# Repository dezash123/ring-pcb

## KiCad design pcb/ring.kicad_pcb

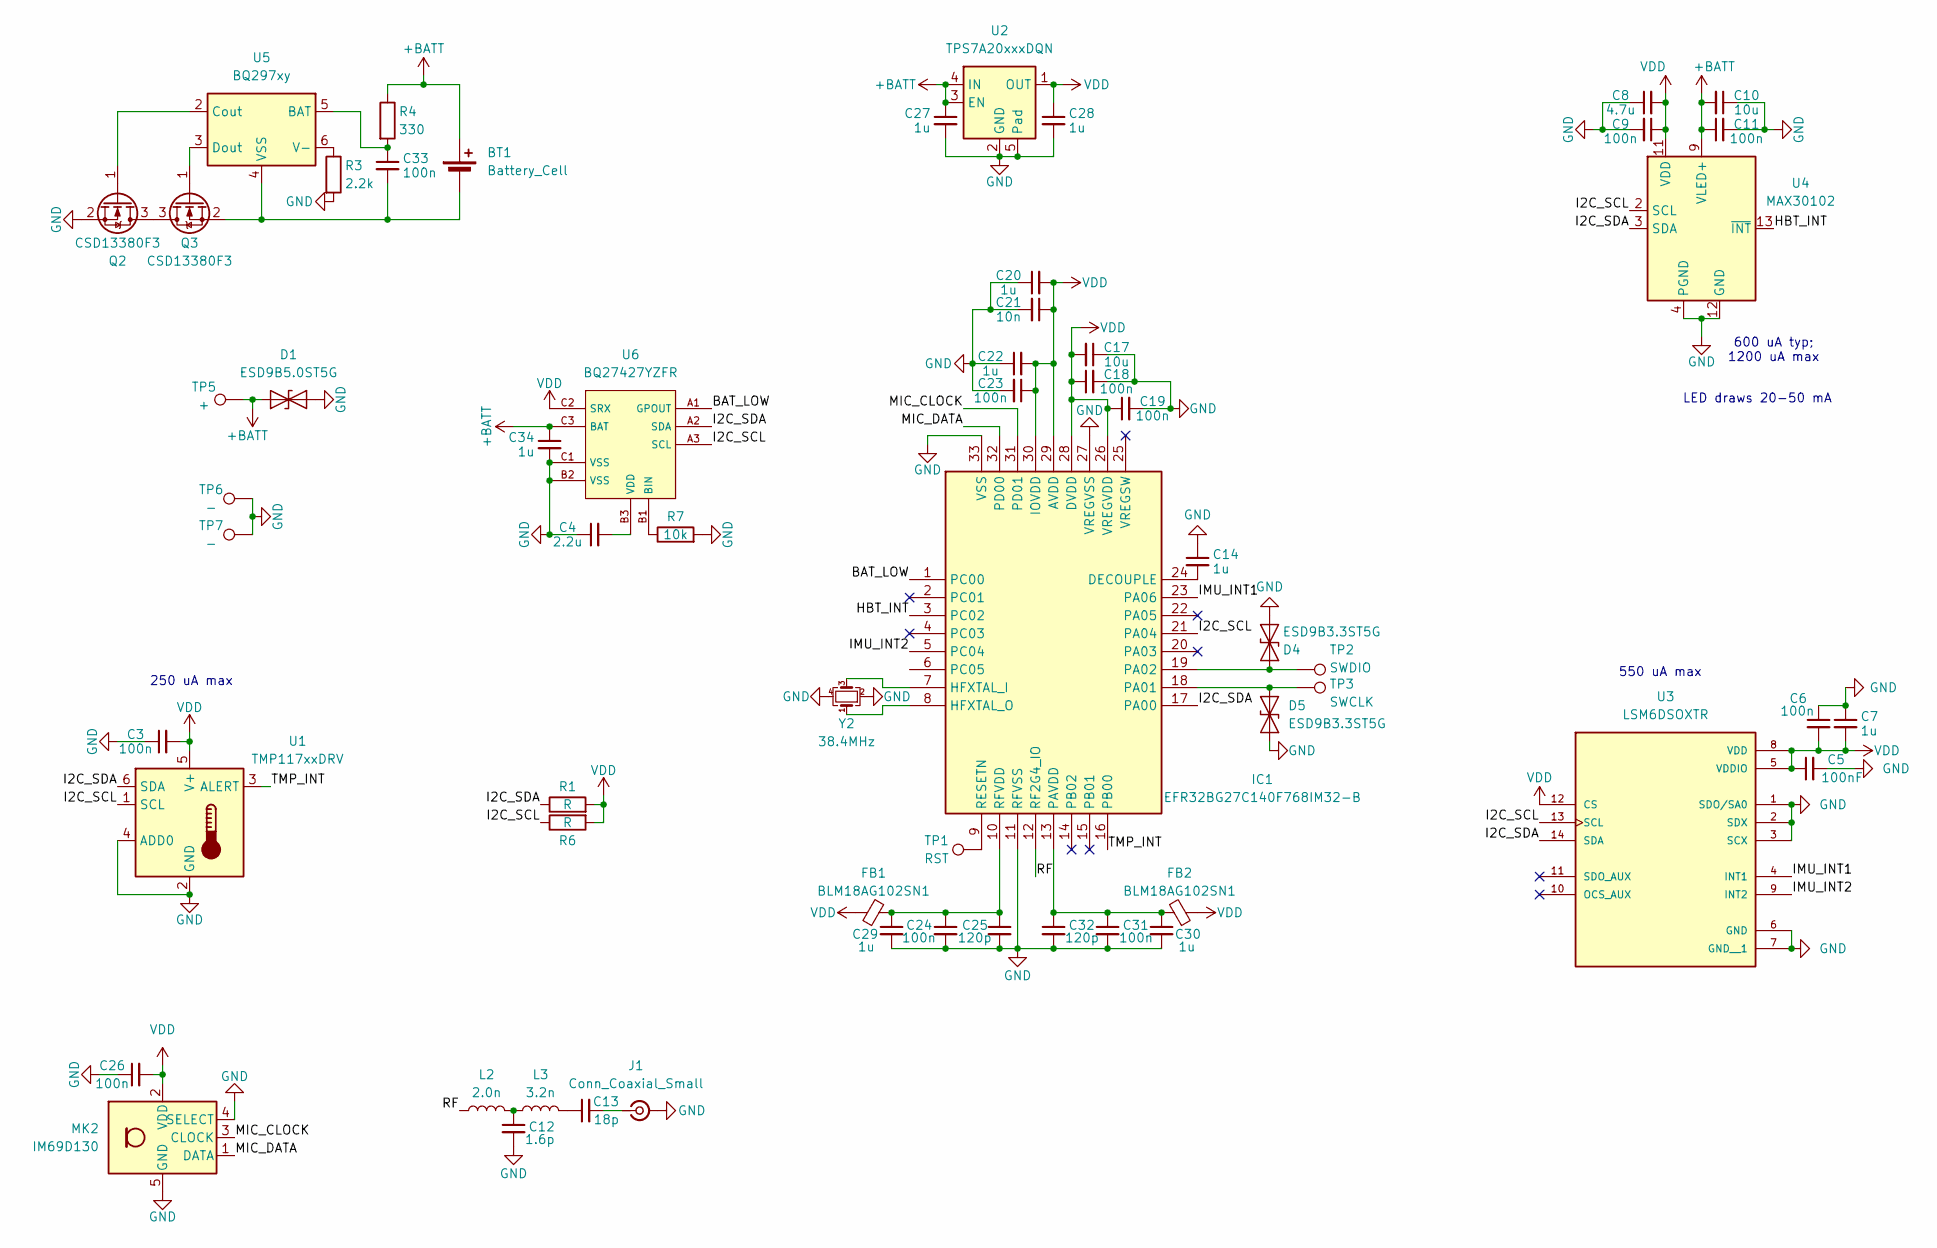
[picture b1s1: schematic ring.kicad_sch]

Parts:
BT1: Battery_Cell; Battery
C3: 100n; R_0201_0603Metric
C4: 2.2u; R_0201_0603Metric
C5: 100nF; C_0201_0603Metric
C6, C9, C11, C18, C19, C23, C24, C26, C31, C33: 100n; C_0201_0603Metric
C7, C14, C20, C22, C27, C28, C29, C30: 1u; C_0402_1005Metric
C8: 4.7u; C_0402_1005Metric
C10, C17: 10u; C_0402_1005Metric
C12: 1.6p; C_0201_0603Metric
C13: 18p; C_0201_0603Metric
C21: 10n; C_0201_0603Metric
C25, C32: 120p; C_0201_0603Metric
C34: 1u; C_0201_0603Metric
D1: ESD9B5.0ST5G; D_SOD-923
D4, D5: ESD9B3.3ST5G; D_SOD-923
FB1, FB2: BLM18AG102SN1; L_0603_1608Metric
IC1: EFR32BG27C140F768IM32-B; QFN-32-1EP_4x4mm_P0.4mm_EP2.9x2.9mm; Mouser Part Number 634-BG27C23068IM32-B
J1: Conn_Coaxial_Small; Texas_SWRA117D_2.4GHz_Right
L2: 2.0n; L_0201_0603Metric
L3: 3.2n; L_0201_0603Metric
MK2: IM69D130; Infineon_PG-LLGA-5-1
Q2, Q3: CSD13380F3; Texas_PicoStar_DFN-3_0.69x0.60mm
R1, R6: R; R_0201_0603Metric
R3: 2.2k; C_0201_0603Metric
R4: 330; C_0201_0603Metric
R7: 10k; R_0201_0603Metric
TP1: RST
TP2: SWDIO; TestPoint_Pad_D1.0mm
TP3: SWCLK; TestPoint_Pad_D1.0mm
TP5: +; TestPoint_Pad_D1.5mm
TP6, TP7: -; TestPoint_Pad_D1.0mm
U1: TMP117xxDRV; WSON-6-1EP_2x2mm_P0.65mm_EP1x1.6mm
U2: TPS7A20xxxDQN; Texas_X2SON-4_1x1mm_P0.65mm
U3: LSM6DSOXTR; LGA-14_3x2.5mm_P0.5mm_LayoutBorder3x4y; PARTREV 3.0
U4: MAX30102; Maxim_OLGA-14_3.3x5.6mm_P0.8mm
U5: BQ297xy; WSON-6_1.5x1.5mm_P0.5mm
U6: BQ27427YZFR; BGA-9_1.6x1.6mm_Layout3x3_P0.5mm
Y2: 38.4MHz; Crystal_SMD_1210-4Pin_1.2x1.0mm

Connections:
+BATT: BT1.1 (+), C10.2, C11.1, C27.1, C34.1, D1.1 (A1), R4.1, TP5.1, U2.3 (EN), U2.4 (IN), U4.9 (VLED+), U4.10 (VLED+), U6.C3 (BAT)
/BAT_LOW: IC1.1 (PC00), U6.A1 (GPOUT)
/HBT_INT: IC1.3 (PC02), U4.13 (~INT)
/I2C_SCL: IC1.21 (PA04), R6.1, U1.1 (SCL), U3.13 (SCL), U4.2 (SCL), U6.A3 (SCL)
/I2C_SDA: IC1.17 (PA00), R1.1, U1.6 (SDA), U3.14 (SDA), U4.3 (SDA), U6.A2 (SDA)
/IMU_INT1: IC1.23 (PA06), U3.4 (INT1)
/IMU_INT2: IC1.5 (PC04), U3.9 (INT2)
/MIC_CLOCK: IC1.31 (PD01), MK2.3 (CLOCK)
/MIC_DATA: IC1.32 (PD00), MK2.1 (DATA)
/RF: IC1.12 (RF2G4_IO), L2.1
/TMP_INT: IC1.16 (PB00), U1.3 (ALERT)
GND: C3.1, C4.1, C5.2, C6.1, C7.1, C8.1, C9.2, C10.1, C11.2, C12.2, C14.1, C17.1, C18.2, C19.2, C20.1, C21.2, C22.1, C23.2, C24.2, C25.2, C26.1, C27.2, C28.2, C29.2, C30.2, C31.2, C32.2, C34.2, D1.2 (A2), D4.2 (A2), D5.1 (A1), IC1.11 (RFVSS), IC1.27 (VREGVSS), IC1.33 (VSS), J1.2 (Ext), MK2.4 (SELECT), MK2.5 (GND), Q2.2 (S), R3.2, R7.2, TP6.1, TP7.1, U1.2 (GND), U1.4 (ADD0), U2.2 (GND), U2.5 (Pad), U3.1 (SDO/SA0), U3.2 (SDX), U3.3 (SCX), U3.6 (GND), U3.7 (GND__1), U4.4 (PGND), U4.12 (GND), U6.B2 (VSS), U6.C1 (VSS), Y2.2, Y2.4
unnamed: BT1.2 (-), C33.2, Q3.2 (S), U5.4 (VSS)
unnamed: C12.1, L2.2, L3.1
unnamed: C13.1, L3.2
unnamed: D4.1 (A1), IC1.19 (PA02), TP2.1
unnamed: D5.2 (A2), IC1.18 (PA01), TP3.1
unnamed: C14.2, IC1.24 (DECOUPLE)
unnamed: IC1.7 (HFXTAL_I), Y2.3
unnamed: IC1.8 (HFXTAL_O), Y2.1
unnamed: C30.1, C31.1, C32.1, FB2.2, IC1.13 (PAVDD)
unnamed: IC1.9 (RESETN), TP1.1
unnamed: C24.1, C25.1, C29.1, FB1.2, IC1.10 (RFVDD)
unnamed: C13.2, J1.1 (In)
unnamed: Q2.3 (D), Q3.3 (D)
unnamed: Q2.1 (G), U5.2 (Cout)
unnamed: Q3.1 (G), U5.3 (Dout)
unnamed: C33.1, R4.2, U5.5 (BAT)
unnamed: R3.1, U5.6 (V-)
unnamed: R7.1, U6.B1 (BIN)
unnamed: C4.2, U6.B3 (VDD)
VDD: C3.2, C5.1, C6.2, C7.2, C8.2, C9.1, C17.2, C18.1, C19.1, C20.2, C21.1, C22.2, C23.1, C26.2, C28.1, FB1.1, FB2.1, IC1.26 (VREGVDD), IC1.28 (DVDD), IC1.29 (AVDD), IC1.30 (IOVDD), MK2.2 (VDD), R1.2, R6.2, U1.5 (V+), U2.1 (OUT), U3.5 (VDDIO), U3.8 (VDD), U3.12 (CS), U4.11 (VDD), U6.C2 (SRX)

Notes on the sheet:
LED draws 20-50 mA
250 uA max
550 uA max
600 uA typ; 1200 uA max

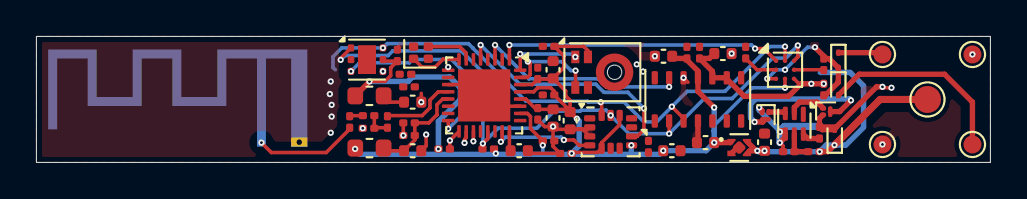
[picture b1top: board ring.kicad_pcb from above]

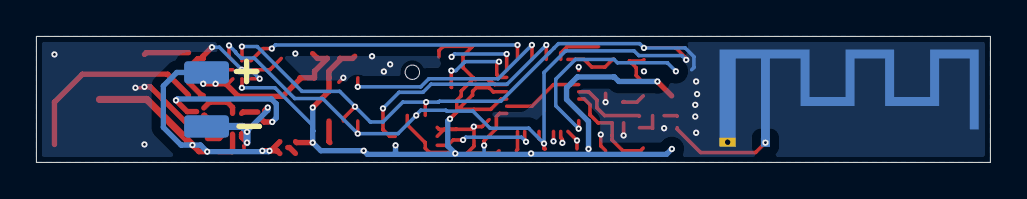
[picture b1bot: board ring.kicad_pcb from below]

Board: 2 copper layers, 53.0 x 7.0 mm, 60 parts (2 on the bottom side), 31 nets.

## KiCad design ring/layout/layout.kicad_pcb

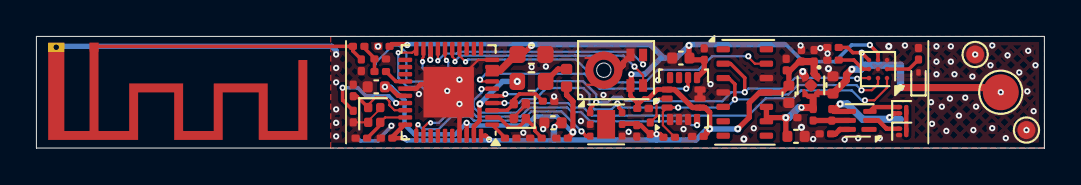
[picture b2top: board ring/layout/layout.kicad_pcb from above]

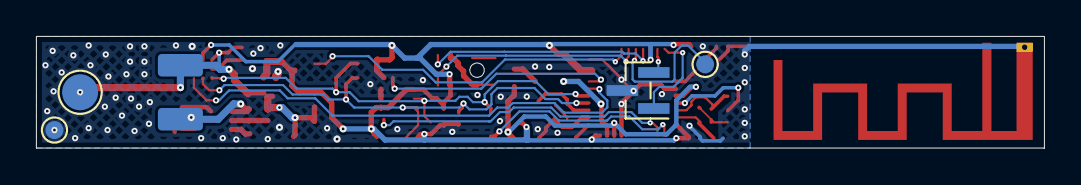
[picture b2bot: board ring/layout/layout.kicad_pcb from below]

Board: 2 copper layers, 56.0 x 6.2 mm, 60 parts (5 on the bottom side), 36 nets.

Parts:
BT1: ?; Battery
C1, C28, C29: 1uF; C_0201_0603Metric
C2: 2.2uF; C_0201_0603Metric
C3, C7, C8, C12, C19, C21, C22, C23, C25, C26: 100nF; C_0201_0603Metric
C4, C9: 5pF; C_0201_0603Metric
C5: 4.7uF; C_0603_1608Metric
C6, C14, C24, C27: 1uF; C_0402_1005Metric
C10, C11: 12pF; C_0201_0603Metric
C13: 100pF; C_0201_0603Metric
C15: 47nF; C_0201_0603Metric
C16: 1pF; C_0201_0603Metric
C17: 1.2pF; C_0201_0603Metric
C18: 10uF; C_0402_1005Metric
C20: 4.7uF; C_0402_1005Metric
D1: ESD9B5.0ST5G; D_SOD-923
J1: ?; Texas_SWRA117D_2.4GHz_Left
L1: 10uH; L_0603_1608Metric
L2: 15nH; L_0402_1005Metric
L3: 4.7nH; L_0201_0603Metric
L4: 2.2nH; L_0201_0603Metric
MK1: IM72D128V01; Infineon_PG-LLGA-5-1
Q1, Q2: CSD13380F3T; Texas_PicoStar_DFN-3_0.69x0.60mm
R1, R2: 4.7k; R_0201_0603Metric
R3: 10k; R_0201_0603Metric
R4: 2.2k; R_0201_0603Metric
R5: 330; R_0201_0603Metric
TP1, TP3, TP4, TP6: TestPoint_Pad_D1.0mm
TP2, TP5: TestPoint_Pad_D2.0mm
U1: BQ27427YZFR; BGA-9_1.6x1.6mm_Layout3x3_P0.5mm
U2: BQ29700; WSON-6_1.5x1.5mm_P0.5mm
U3: nRF52833-QDAA; Modified_QFN-40_5.0mmx5.0mm
U4: MAX30102EFD+T; Maxim_OLGA-14_3.3x5.6mm_P0.8mm
U5: LSM6DSOX; LGA-14_3x2.5mm_P0.5mm_LayoutBorder3x4y
U6: ?; PinHeader_1x03_P1.00mm_Vertical_SMD_Pin1Left
U7: TMP117AIDRVR; WSON-6-1EP_2x2mm_P0.65mm_EP1x1.6mm
U8: TPS7A2018PDQN; Texas_X2SON-4_1x1mm_P0.65mm
Y1: 8J32076001; Crystal_SMD_1210-4Pin_1.2x1.0mm
Y2: 3110M4-32.768DTTLLLL; Crystal_SMD_1210-4Pin_1.2x1.0mm

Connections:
GND: C1.2, C2.2, C4.2, C5.2, C6.2, C7.2, C8.2, C9.2, C10.2, C11.2, C12.2, C13.2, C14.2, C15.2, C16.2, C17.2, C18.2, C19.2, C20.2, C21.2, C22.2, C23.2, C24.2, C25.2, C26.2, C27.2, C28.2, C29.2, D1.2, J1.2, MK1.4, MK1.5, Q2.2, R3.2, R4.2, TP3.1, TP4.1, TP6.1, U1.B2, U1.C1, U3.10, U3.25, U3.37, U3.41, U4.4, U4.12, U5.1, U5.2, U5.3, U5.6, U5.7, U6.2, U7.2, U7.4, U8.2, U8.5, Y1.2, Y1.4, Y2.2, Y2.4
VBATT: BT1.1, C1.1, C18.1, C19.1, C27.1, D1.1, R5.1, TP2.1, TP5.1, U1.C3, U4.9, U4.10, U8.3, U8.4
VDD: C5.1, C6.1, C7.1, C8.1, C20.1, C21.1, C22.1, C23.1, C24.1, C25.1, C26.1, C28.1, C29.1, MK1.2, R1.1, R2.1, U1.C2, U3.8, U3.9, U3.18, U3.30, U3.40, U4.11, U5.5, U5.8, U5.12, U7.5, U8.1
bat_low: U1.A1, U3.6
batman.batman_vdd_out: C2.1, U1.B3
batman.bin: R3.1, U1.B1
battery.bat2: C3.1, R5.2, U2.5
battery.bat_cout: Q2.1, U2.2
battery.bat_dout: Q1.1, U2.3
battery.bat_qm: Q1.3, Q2.3
battery.bat_vm: R4.1, U2.6
battery.bat_vss: BT1.2, C3.2, Q1.2, U2.4
cpu.ant: L3.1, U3.24
cpu.antenna.n1: C16.1, L3.2, L4.1
cpu.antenna.n2: C17.1, J1.1, L4.2
cpu.dcc: L1.1, U3.39
cpu.dcc_mid: L1.2, L2.1
cpu.dec1: C12.1, U3.1
cpu.dec3: C13.1, U3.27
cpu.dec4_6: C14.1, C15.1, L2.2, U3.26, U3.38
cpu.xin: C4.1, U3.28, Y1.1
cpu.xl1: C10.1, U3.2, Y2.1
cpu.xl2: C11.1, U3.3, Y2.3
cpu.xout: C9.1, U3.29, Y1.3
hbt.NC: U4.1, U4.5, U4.6, U4.7, U4.8, U4.14
hbt_int: U3.14, U4.13
imu_int1: U3.32, U5.4
imu_int2: U3.7, U5.9
mic_clk: MK1.3, U3.17
mic_data: MK1.1, U3.15
rst: TP1.1, U3.16
scl: R2.2, U1.A3, U3.5, U4.2, U5.13, U7.1
sda: R1.2, U1.A2, U3.4, U4.3, U5.14, U7.6
swdclk: U3.20, U6.1
swdio: U3.19, U6.3
tmp_int: U3.31, U7.3

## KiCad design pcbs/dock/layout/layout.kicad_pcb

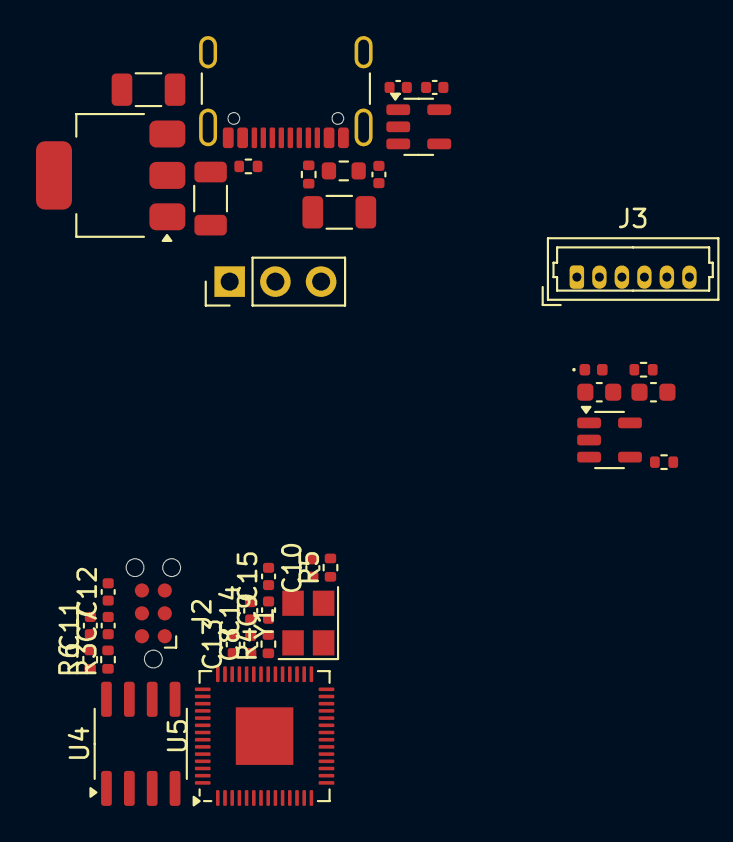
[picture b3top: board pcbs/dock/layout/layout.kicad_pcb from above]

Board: 2 copper layers, 37 parts (0 on the bottom side), 22 nets, no tracks yet.

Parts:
C1, C2: 4.7uF 10V; C_0603_1608Metric
C3, C8, C12, C13: 1uF 10V; C_0402_1005Metric
C4: 1uF 6.3V; C_0402_1005Metric
C5, C16: 10uF 16V; C_1206_3216Metric
C6: 10uF 10V; C_1206_3216Metric
C7, C11: 100nF 10V; C_0402_1005Metric
C9, C10: 100nF 6.3V; C_0402_1005Metric
C14, C15: 10pF 50V; C_0402_1005Metric
C17: 100nF 16V; C_0402_1005Metric
D1: LED RED; LED_0402_1005Metric
FB1: 120 100MHz; R_0603_1608Metric
J1: PinHeader_1x03_P2.54mm_Vertical
J2: ?; Tag-Connect_TC2030-IDC-NL_2x03_P1.27mm_Vertical
J3: 53047-0610; Molex_PicoBlade_53047-0610_1x06_P1.25mm_Vertical
R1: 2k 1%; R_0402_1005Metric
R2: 1k; R_0402_1005Metric
R3, R6: 10k; R_0402_1005Metric
R4, R5: 27; R_0402_1005Metric
R7, R8: 5.1k 1%; R_0402_1005Metric
U1: MCP73831T-2ACI/OT; SOT-23-5
U2: AP2112K-1.8TRG1; SOT-23-5
U3: AMS1117-3.3; SOT-223
U4: MX25R3235FM1IH0; SOIC-8_3.9x4.9mm_P1.27mm
U5: RP2040; QFN-56-1EP_7x7mm_P0.4mm_EP3.2x3.2mm
U6: ?; USB_C_Receptacle_GCT_USB4105-xx-A_16P_TopMnt_Horizontal
Y1: 12MHz 10pF; Crystal_SMD_3225-4Pin_3.2x2.5mm

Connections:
charger.CHG_STAT: R2.1, U1.1
charger.ISET: R1.1, U1.5
charger.LED_A: D1.2, R2.2
gnd: C1.2, C2.2, C3.2, C4.2, C5.2, C6.2, C7.2, C8.2, C9.2, C10.2, C11.2, C12.2, C13.2, C14.2, C15.2, C16.2, C17.2, D1.1, J1.1, J1.3, J2.5, J3.2, R1.2, R7.2, R8.2, U1.2, U2.2, U3.1, U4.4, U5.19, U5.57, U6.A1, U6.A12, U6.B1, U6.B12, U6.S1, Y1.2, Y1.4
probe.ADC_AVDD: C7.1, C8.1, U5.43
probe.VREG_VOUT: C13.1, U5.23, U5.45, U5.50
probe.XIN: C14.1, U5.20, Y1.1
probe.XOUT: C15.1, U5.21, Y1.3
probe.usb_dm_mcu: R4.1, U5.46
probe.usb_dp_mcu: R5.1, U5.47
probe_nreset: J2.3, U5.26
probe_swclk: J2.4, U5.5
probe_swdio: J2.2, U5.4
usb.CC1: R7.1, U6.A5
usb.CC2: R8.1, U6.B5
usb.VBUS_RAW: FB1.1, U6.A4, U6.A9, U6.B4, U6.B9
usb_dm: R4.2, U6.A7, U6.B7
usb_dp: R5.2, U6.A6, U6.B6
vbatt: C1.1, J1.2, U1.3
vbus_5v: C2.1, C3.1, C5.1, C16.1, C17.1, FB1.2, J3.1, U1.4, U2.1, U2.3, U3.3
vdd_1v8: C4.1, C9.1, C10.1, C12.1, J2.1, R3.2, R6.2, U2.5, U4.8, U5.1, U5.10, U5.22, U5.33, U5.42, U5.44, U5.49
vdd_3v3: C6.1, C11.1, U3.2, U5.48

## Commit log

2025-09-07 init
2025-09-09 schematic basically done
2025-09-10 battery protection
2025-09-11 switched to smaller battery, will be removing external protection
2025-09-14 pcb laid out, schematic done
2025-09-18 nearly done routing
2025-09-20 moving to using zener
2025-09-21 added in rf power
2025-09-21 finished port and antenna in zener
2025-09-21 zener layout done; nets named and final passives added
2025-09-21 laid out pcb and began routing (6.2mm tall!)
2025-09-21 board fully routed; fixing DRC
2025-09-21 pretty rounded tracks; breaks everything though
2025-09-23 drc passes
2025-09-27 added nrf5340
2025-09-27 replaced mcu, removed old connections in layout
2025-09-28 nrf laid out but unrouted; probably have to switch for manufacturing
2025-09-28 init esp32h2
2025-09-28 reorganize
2025-09-28 layout and custom footprint for clearance
2025-09-29 routed
2025-09-29 rounded
2025-09-29 reounded done
2025-09-29 add mpns
2025-09-30 all mpns
2025-09-30 envrc
2025-10-03 more vias
2025-10-03 cleanup
2025-10-03 two-sided port
2025-10-03 dock
2025-10-05 change port spacing
2025-10-05 teardrops
2025-10-12 reorganizing
2025-10-12 changed connector
2025-10-12 reroute
2025-10-12 update rounded board
2025-10-12 added crystal mpns and updated caps
2025-10-13 dock updates
2025-10-13 reorganized for v2
2025-10-13 rounded v2
2025-10-14 change to 3v3
2025-10-14 change to 3.3V
2025-10-15 smaller batmon courtyard
2025-10-15 temp
2025-10-15 stricter DRC
2025-10-16 stricterer DRC
2025-11-11 rerouted a bit
2025-11-14 reorganization
2025-11-14 more reorganization
